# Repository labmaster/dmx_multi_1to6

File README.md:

# dmx_multi_1to6
a DIN rail device with a width of 4 modules that receives one DMX Bus signal and multiplies it to 6 DMX Bus Signals

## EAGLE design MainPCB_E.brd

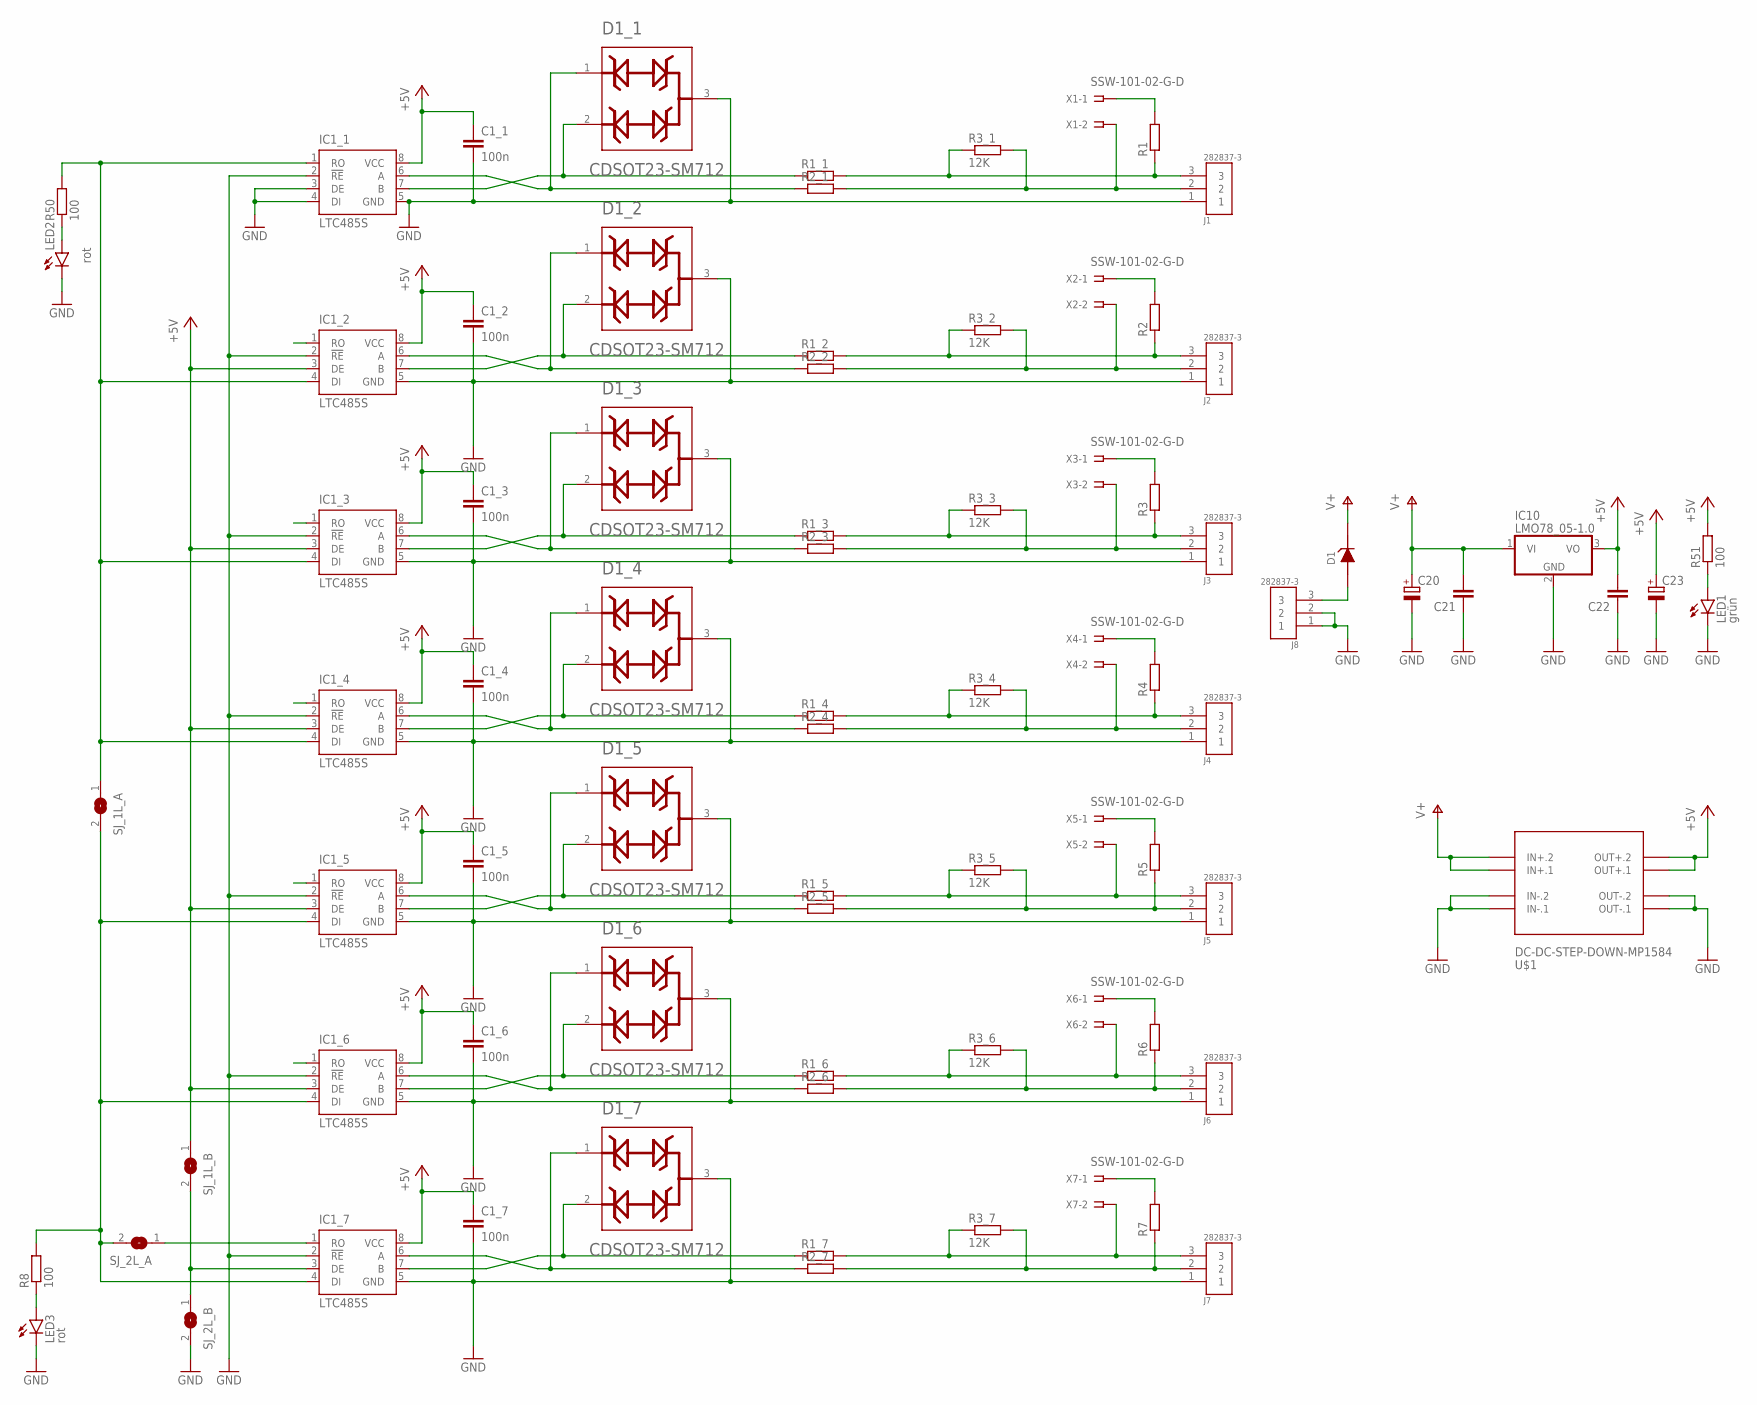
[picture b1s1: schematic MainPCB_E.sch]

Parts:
C1_1, C1_2, C1_3, C1_4, C1_5, C1_6, C1_7: 100n; C0603K
C20, C23: CPOL-EUE5-8.5; E5-8,5
C21, C22: C-EUC0805K; C0805K
D1: ZMM; MINIMELF
D1_1, D1_2, D1_3, D1_4, D1_5, D1_6, D1_7: BOURNS_INC._CDSOT23-SM712BOURNS_INC._CDSOT23-SM71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; BOURNS_INC._CDSOT23-SM712_1
IC1_1, IC1_2, IC1_3, IC1_4, IC1_5, IC1_6, IC1_7: LTC485S; SOIC8
IC10: LMO78_05-1.0; TO220V
J1, J2, J3, J4, J5, J6, J7, J8: 282837-3; TE_282837-3
LED1: grün; LED5MM
LED2, LED3: rot; LED5MM
R1, R2, R3, R4, R5, R6, R7: R-EU_R1206; R1206
R1_1, R1_2, R1_3, R1_4, R1_5, R1_6, R1_7, R2_1, R2_2, R2_3, R2_4, R2_5, R2_6, R2_7: R-EU_R0805; R0805
R3_1, R3_2, R3_3, R3_4, R3_5, R3_6, R3_7: 12K; R0603
R8, R50, R51: 100; R0603
SJ_1L_A, SJ_1L_B, SJ_2L_A, SJ_2L_B: SJ
U$1: DC-DC-STEP-DOWN-MP1584
X1, X2, X3, X4, X5, X6, X7: SSW-101-02-G-D

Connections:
+5V: C1_1.1, C1_2.1, C1_3.1, C1_4.1, C1_5.1, C1_6.1, C1_7.1, C22.2, C23.+, IC1_1.8 (VCC), IC1_2.3 (DE), IC1_2.8 (VCC), IC1_3.3 (DE), IC1_3.8 (VCC), IC1_4.3 (DE), IC1_4.8 (VCC), IC1_5.3 (DE), IC1_5.8 (VCC), IC1_6.3 (DE), IC1_6.8 (VCC), IC1_7.8 (VCC), IC10.3 (VO), R51.2, SJ_1L_B.1, U$1.OUT+.1, U$1.OUT+.2
GND: C1_1.2, C1_2.2, C1_3.2, C1_4.2, C1_5.2, C1_6.2, C1_7.2, C20.-, C21.1, C22.1, C23.-, D1_1.3, D1_2.3, D1_3.3, D1_4.3, D1_5.3, D1_6.3, D1_7.3, IC1_1.2 (!RE), IC1_1.3 (DE), IC1_1.4 (DI), IC1_1.5 (GND), IC1_2.2 (!RE), IC1_2.5 (GND), IC1_3.2 (!RE), IC1_3.5 (GND), IC1_4.2 (!RE), IC1_4.5 (GND), IC1_5.2 (!RE), IC1_5.5 (GND), IC1_6.2 (!RE), IC1_6.5 (GND), IC1_7.2 (!RE), IC1_7.5 (GND), IC10.2 (GND), J1.1, J2.1, J3.1, J4.1, J5.1, J6.1, J7.1, J8.1, J8.2, LED1.K (C), LED2.K (C), LED3.K (C), SJ_2L_B.2, U$1.IN-.1, U$1.IN-.2, U$1.OUT-.1, U$1.OUT-.2
unnamed: R7.2, X7.1
unnamed: R6.2, X6.1
unnamed: LED3.A, R8.1
unnamed: R5.2, X5.1
unnamed: D1_1.2, IC1_1.7 (B), R1_1.1
unnamed: IC1_7.3 (DE), SJ_1L_B.2, SJ_2L_B.1
unnamed: IC1_1.1 (RO), IC1_2.4 (DI), IC1_3.4 (DI), IC1_4.4 (DI), R50.2, SJ_1L_A.1
unnamed: J1.3, R1.1, R1_1.2, R3_1.1
unnamed: J1.2, R2_1.2, R3_1.2, X1.2
unnamed: D1_1.1, IC1_1.6 (A), R2_1.1
unnamed: R4.2, X4.1
unnamed: R3.2, X3.1
unnamed: R2.2, X2.1
unnamed: D1_2.2, IC1_2.7 (B), R1_2.1
unnamed: J2.3, R1_2.2, R2.1, R3_2.1
unnamed: J2.2, R2_2.2, R3_2.2, X2.2
unnamed: IC1_7.1 (RO), SJ_2L_A.1
unnamed: D1_2.1, IC1_2.6 (A), R2_2.1
unnamed: R1.2, X1.1
unnamed: D1_3.2, IC1_3.7 (B), R1_3.1
unnamed: J3.3, R1_3.2, R3.1, R3_3.1
unnamed: J3.2, R2_3.2, R3_3.2, X3.2
unnamed: D1_3.1, IC1_3.6 (A), R2_3.1
unnamed: J4.3, R1_4.2, R3_4.1, R4.1
unnamed: J4.2, R2_4.2, R3_4.2, X4.2
unnamed: IC1_5.4 (DI), IC1_6.4 (DI), IC1_7.4 (DI), R8.2, SJ_1L_A.2, SJ_2L_A.2
unnamed: J5.3, R1_5.2, R3_5.1, X5.2
unnamed: J5.2, R2_5.2, R3_5.2, R5.1
unnamed: J6.3, R1_6.2, R3_6.1, X6.2
unnamed: J6.2, R2_6.2, R3_6.2, R6.1
unnamed: J7.3, R1_7.2, R3_7.1, X7.2
unnamed: J7.2, R2_7.2, R3_7.2, R7.1
unnamed: D1_5.2, IC1_5.7 (B), R1_5.1
unnamed: D1.A, J8.3
unnamed: LED1.A, R51.1
unnamed: LED2.A, R50.1
unnamed: D1_5.1, IC1_5.6 (A), R2_5.1
unnamed: D1_6.2, IC1_6.7 (B), R1_6.1
unnamed: D1_6.1, IC1_6.6 (A), R2_6.1
unnamed: D1_4.2, IC1_4.7 (B), R1_4.1
unnamed: D1_4.1, IC1_4.6 (A), R2_4.1
unnamed: D1_7.2, IC1_7.7 (B), R1_7.1
unnamed: D1_7.1, IC1_7.6 (A), R2_7.1
V+: C20.+, C21.2, D1.C (K), IC10.1 (VI), U$1.IN+.1, U$1.IN+.2

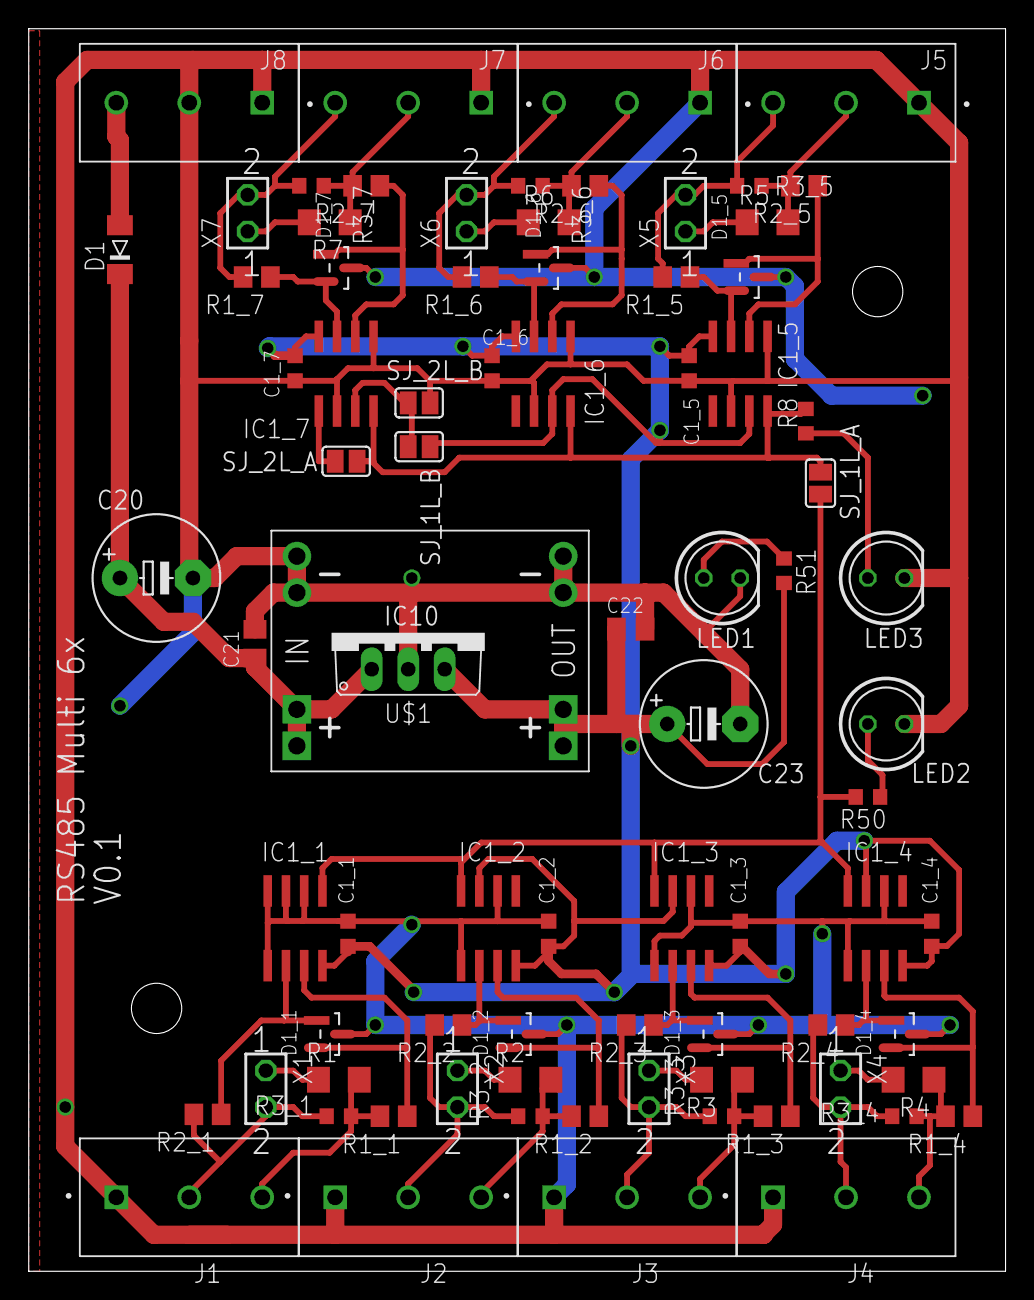
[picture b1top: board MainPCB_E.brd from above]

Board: 2 copper layers, 68.0 x 86.5 mm, 81 parts (0 on the bottom side), 46 nets.

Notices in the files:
parts and their libraries:
diy-modules: Released under the Creative Commons Attribution 4.0 International License: http://creativecommons.org/licenses/by/4.0
